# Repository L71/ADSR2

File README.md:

ADSR2
=====

Eurorack CMOS logic ADSR envelope generator.

* adsr2 - original version, based on separate switch ic and demultiplexer. (this one has known design bugs).

* adsr2v2 - use a dual switch multiplexer/demultiplexer for everything. Should work, but will likely not be prototyped.

* adsr2v3 - improved v2, use a 40106 buffer/inverter for IO buffers instead of transistors (=lower component count). Prototype build looks and works exactly as intended. :)

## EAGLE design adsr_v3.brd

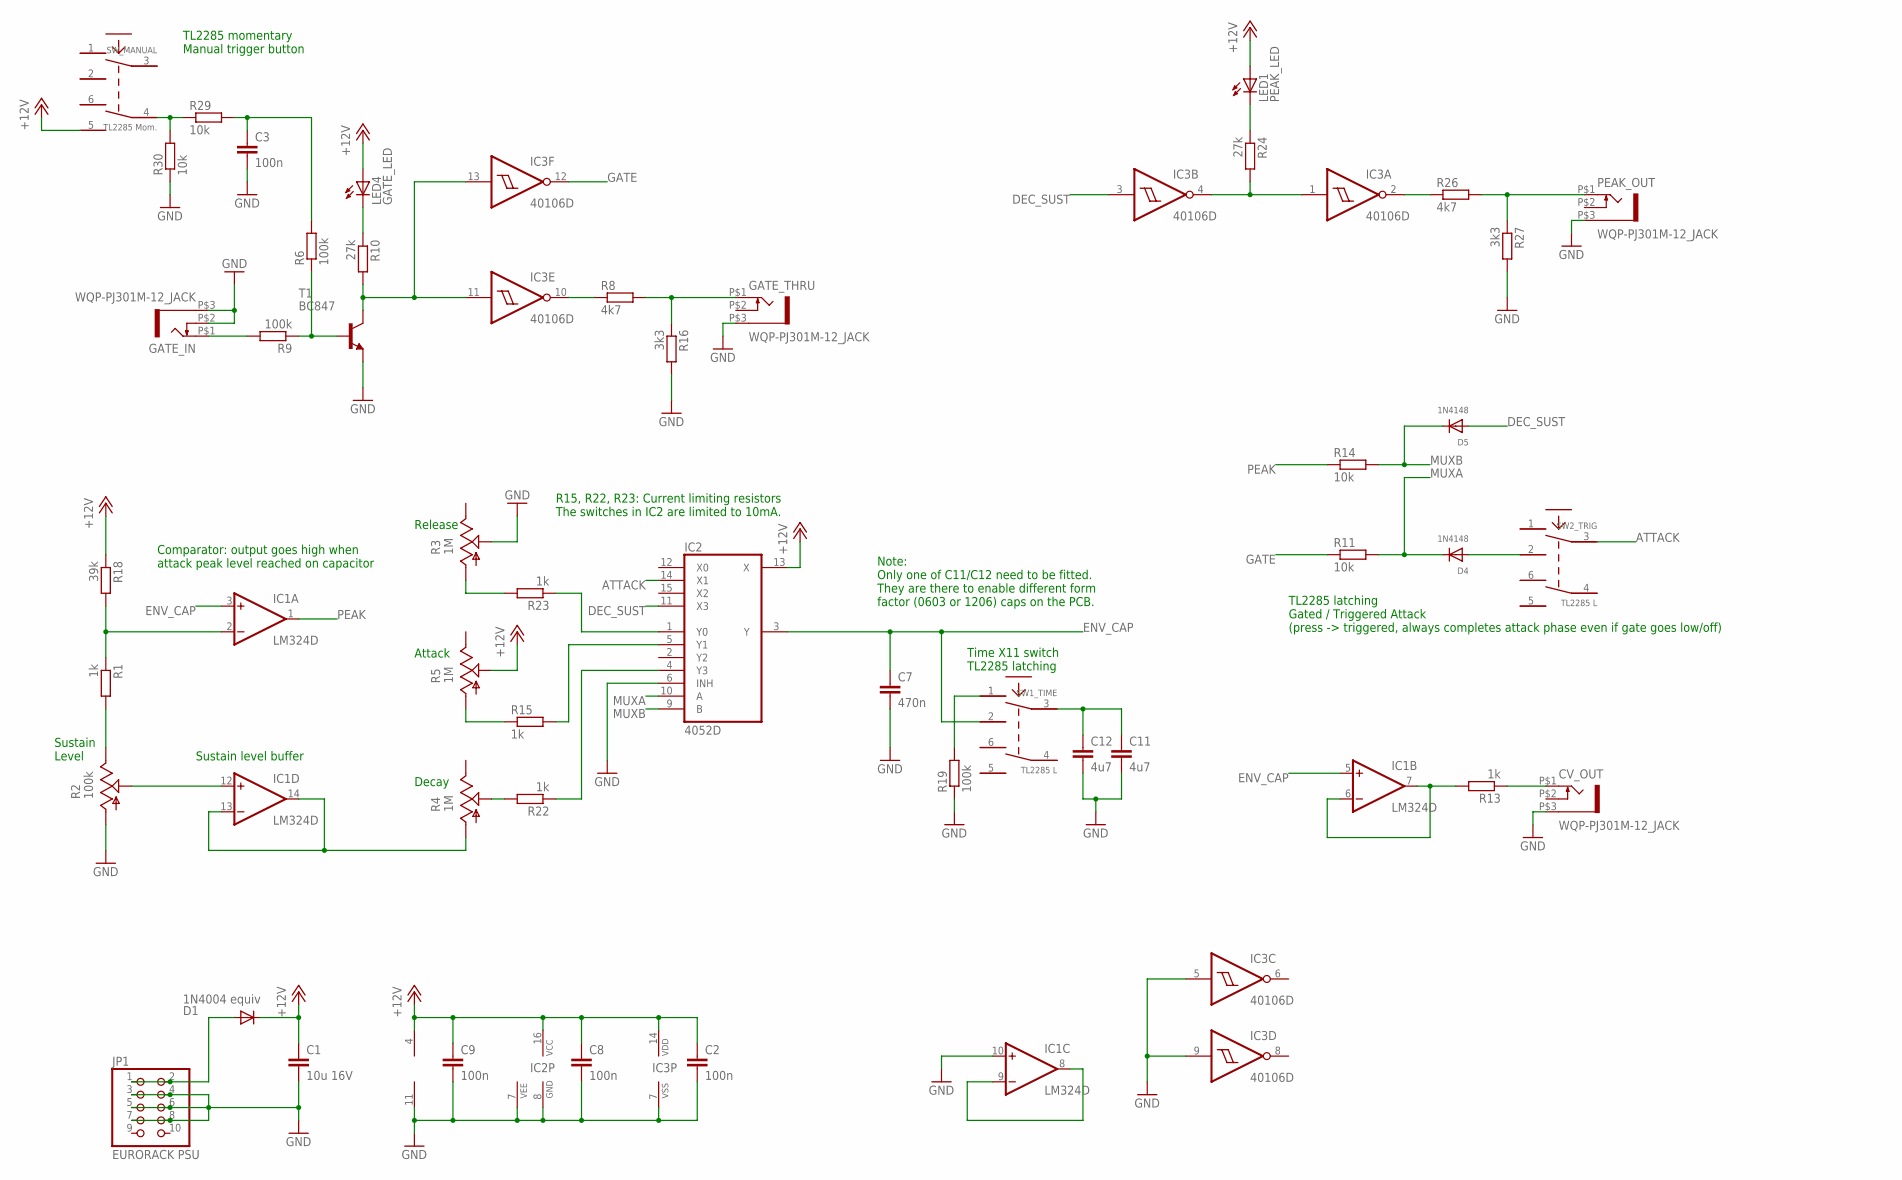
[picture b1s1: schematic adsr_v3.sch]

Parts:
C1: 10u 16V; C1206K
C2, C3, C8, C9: 100n; C0603K
C7: 470n; C0603K
C11: 4u7; C1206K
C12: 4u7; C0603K
CV_OUT: WQP-PJ301M-12_JACK
D1: 1N4004 equiv; DO214AA
D4, D5: 1N4148; SOD-323F
GATE_IN: WQP-PJ301M-12_JACK
GATE_THRU: WQP-PJ301M-12_JACK
IC1: LM324D; SO14
IC2: 4052D; SO16
IC3: 40106D; SO14
JP1: EURORACK PSU; 2X05
LED1: PEAK_LED; LED5MM
LED4: GATE_LED; LED5MM
PEAK_OUT: WQP-PJ301M-12_JACK
R1, R13, R15, R22, R23: 1k; R0603
R2: 100k; ALPS_POT_VERTICAL
R3, R4, R5: 1M; ALPS_POT_VERTICAL
R6, R9, R19: 100k; R0603
R8, R26: 4k7; R0603
R10, R24: 27k; R0603
R11, R14, R29, R30: 10k; R0603
R16, R27: 3k3; R0603
R18: 39k; R0603
SW1_TIME, SW2_TRIG: TL2285 L; TL2285_PCB
SW_MANUAL: TL2285 Mom.; TL2285_PCB
T1: BC847; SOT23

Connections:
+12V: C1.1, C2.1, C8.1, C9.1, D1.C, IC1.4 (V+), IC2.13 (X), IC2.16 (VCC), IC3.14 (VDD), LED1.A, LED4.A, R5.P$2 (S), R18.1, SW_MANUAL.5
ATTACK: IC2.14 (X1), SW2_TRIG.3
ATTACK_REF: IC1.2 (-IN), R1.1, R18.2
DEC_SUST: D5.A, IC2.11 (X3), IC3.3 (I)
ENV_CAP: C7.1, IC1.3 (+IN), IC1.5 (+IN), IC2.3 (Y), SW1_TIME.2
GATE: IC3.12 (O), R11.1
GATE_IN: IC3.11 (I), IC3.13 (I), R10.2, T1.3 (C)
GND: C1.2, C2.2, C3.2, C7.2, C8.2, C9.2, C11.2, C12.2, CV_OUT.P$3 (1), GATE_IN.P$2 (3), GATE_IN.P$3 (1), GATE_THRU.P$3 (1), IC1.10 (+IN), IC1.11 (V-), IC2.6 (INH), IC2.7 (VEE), IC2.8 (GND), IC3.5 (I), IC3.7 (VSS), IC3.9 (I), JP1.3, JP1.4, JP1.5, JP1.6, JP1.7, JP1.8, PEAK_OUT.P$3 (1), R2.P$3 (A), R3.P$2 (S), R16.2, R19.1, R27.2, R30.1, T1.2 (E)
MUXA: D4.C, IC2.10 (A), R11.2
MUXB: D5.C, IC2.9 (B), R14.2
unnamed: IC3.10 (O), R8.1
unnamed: GATE_IN.P$1 (2), R9.2
unnamed: D1.A, JP1.1, JP1.2
unnamed: R29.1, R30.2, SW_MANUAL.4
unnamed: IC2.1 (Y0), R23.1
unnamed: IC2.4 (Y3), R22.1
unnamed: IC1.13 (-IN), IC1.14 (OUT), R4.P$3 (A)
unnamed: IC3.2 (O), R26.1
unnamed: IC2.5 (Y1), R15.2
unnamed: CV_OUT.P$1 (2), R13.1
unnamed: IC1.6 (-IN), IC1.7 (OUT), R13.2
unnamed: GATE_THRU.P$1 (2), R8.2, R16.1
unnamed: C3.1, R6.2, R29.2
unnamed: C11.1, C12.1, SW1_TIME.3
unnamed: R19.2, SW1_TIME.1
unnamed: R6.1, R9.1, T1.1 (B)
unnamed: LED4.K (C), R10.1
unnamed: R3.P$3 (A), R23.2
unnamed: IC1.8 (OUT), IC1.9 (-IN)
unnamed: R5.P$3 (A), R15.1
unnamed: R1.2, R2.P$1 (E)
unnamed: D4.A, SW2_TRIG.2
unnamed: R4.P$2 (S), R22.2
unnamed: IC3.1 (I), IC3.4 (O), R24.2
unnamed: LED1.K (C), R24.1
unnamed: PEAK_OUT.P$1 (2), R26.2, R27.1
PEAK: IC1.1 (OUT), R14.1
SUST_LEVEL: IC1.12 (+IN), R2.P$2 (S)

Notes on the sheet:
Time X11 switch TL2285 latching
Note: Only one of C11/C12 need to be fitted. They are there to enable different form factor (0603 or 1206) caps on the PCB.
TL2285 latching Gated / Triggered Attack (press -> triggered, always completes attack phase even if gate goes low/off)
Sustain level buffer
Comparator: output goes high when attack peak level reached on capacitor
R15, R22, R23: Current limiting resistors The switches in IC2 are limited to 10mA.
TL2285 momentary Manual trigger button
Attack
Release
Decay
Sustain Level

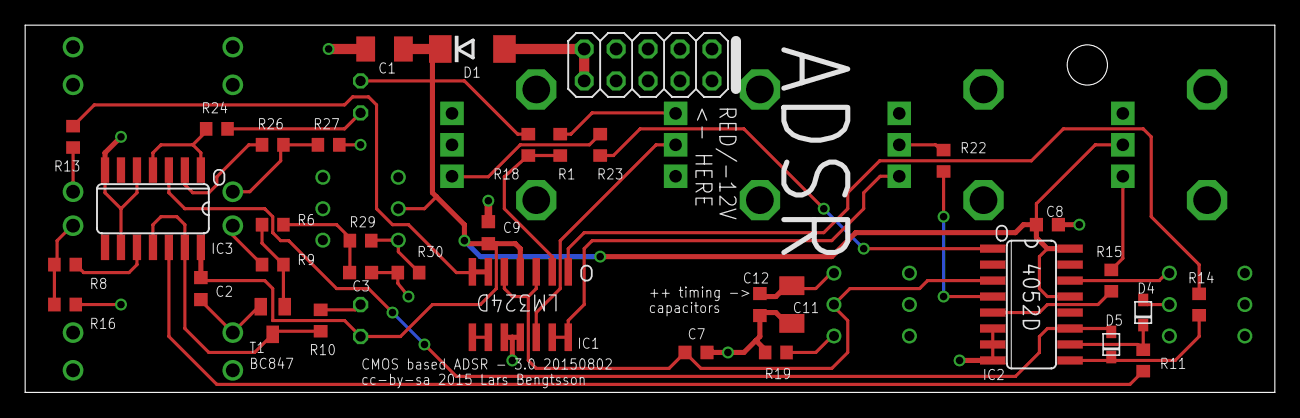
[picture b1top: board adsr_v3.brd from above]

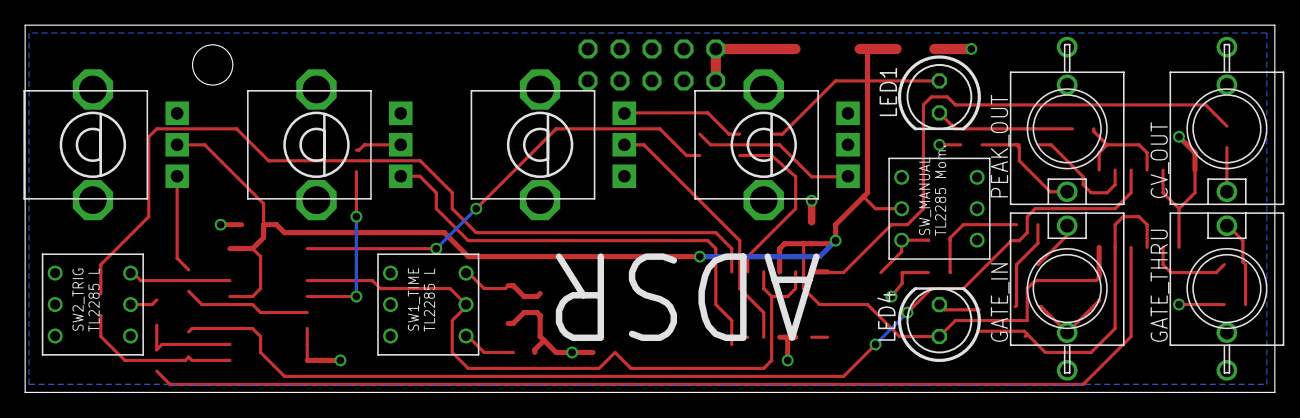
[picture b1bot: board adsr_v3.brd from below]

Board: 2 copper layers, 99.4 x 29.2 mm, 48 parts (13 on the bottom side), 38 nets.

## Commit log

2015-07-05 Initial commit.
2015-07-07 Board added. Status LEDs removed (only GATE indicator left)
2015-07-11 Changed gate IO and outputs: Gate in, Gate thru, "Attack done" trigger out, Envelope CV Out. Removed gate thru mode selector switch. Added LED #2 for "attack done" trigger. Adjusted component labels 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
2015-07-12 Minor routing fixes & components moved.
2015-07-12 Some more routing fixes near jacks. Updated date stamp in PCB text labels.
2015-07-12 Oops, missed 2.5mm of 12V net. fixed.
2015-07-12 Initial panel design (follows Ponoko.com guidelines).
2015-07-12 No CAPITALS except in label at the top.
2015-07-18 Initial commit of V2 - design with cd4052 dual multiplexer. Down to 2 ICs, much simpler PCB.
2015-07-18 Renamed comparator output net to "peak". Minor routing fixes on PCB.
2015-07-18 Modified some text notes.
2015-07-18 Changed R1 to 1k.
2015-07-18 Changed LEDs to 5mm footprint. Moved T3 and surrounding resistors a bit.
2015-07-19 Bigger button holes (6mm, was 5mm). Changed line width to .01 mm as per Ponoko laser cutting specs.
2015-07-20 Added circuit to make sure peak output pulse has at least a few ms duration. Changed peak output to behave like decay+sustain gate rather than just "attack done" trigger output.
2015-07-20 Small routing adjustments.
2015-07-23 Moved power diode and cap a bit to make it easier to solder components around PSU header/release pot.
2015-07-31 Fixed direction of potentiometers. Added debouncing circuit for manual trig button. Updated date/version label.
2015-08-02 Add v3. Replaces most transistor buffers with pieces of a 40106. Simplified diode logic too.
2015-08-02 Added info about revisions.
2015-08-02 Moved PSU capacitor a bit.
2015-08-02 Updated info.
2015-08-02 Minor routing & labeling fixes. Replaced schematic A3 document frame with other type.
2015-08-04 Moved PSU diode and capacitor a bit. Diode has a rather bit and wide package, we better leave a bit of space around it.
2015-08-08 Changed some resistors from 100k to 10k; this works with the used BC847 transistors. (Breadboard prototype used BC547B)
2015-08-20 Changed LED current resistors to 27k, better match with the 350-400 mcd LEDs.
2015-08-22 Updated readme after prototyping of v3.
2015-09-27 Added hole. Needed to hold front panel in place when panel can't be held in place by potentiometers.
2016-01-11 Adjusted panel bottom edge and holes downwards 1/40" to better fit racks w 3mm screws.

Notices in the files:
adsr_v3.brd:
cc-by-sa 2015 Lars Bengtsson
